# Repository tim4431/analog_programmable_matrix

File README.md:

# Analog Programmable Matrix

A four-input, four-output, DC-coupled analog matrix for programmable addition, subtraction, and signal mixing. A Raspberry Pi Pico sets sixteen static signed coefficients over USB; the signals remain in the analog domain.

$$b_i = \sum_{j=0}^{3} M_{ij}a_j, \qquad -1 \leq M_{ij} \leq 1$$

This first public version contains **PCB D and enclosure M3**, without the added power-indicator LED. It is an **unbuilt prototype**: the 1 MHz bandwidth and approximately 1% gain accuracy are design targets supported by circuit simulations, not measured hardware specifications.

A separate **[LC1 lower-cost 12-bit design](variants/lc1/README.md)** is also included. It preserves the original design and enclosure interface, reduces the listed component count from 428 to 387, and replaces the expensive multiplying DACs. LC1 has its own schematic, PCB, firmware, sourcing notes and simulation evidence. The renders below show the original Revision D.

## PCB and enclosure

These are renders generated from the CAD, not photographs of manufactured hardware.

[Exploded enclosure render](mechanical/analog_matrix_package_m3/renders/enclosure_exploded.png) · [Dimensioned drawing](mechanical/analog_matrix_package_m3/mechanical_dimensions.png)

## Design at a glance

| Item | Design |
| --- | --- |
| Matrix | 4 × 4, independently programmable signed coefficients |
| Signal range | DC through 1 MHz target; ±1 V peak per input |
| Inputs | Four vertical BNCs; high impedance by default |
| Outputs | Four vertical BNCs; up to ±4 V peak **into an external 50 Ω load** |
| Output termination | 49.9 Ω series source resistor; a high-impedance receiver sees approximately twice the loaded voltage |
| Coefficient control | 16-bit multiplying DACs and analog polarity switches |
| Controller | Original Raspberry Pi Pico, MicroPython, USB serial JSON commands |
| Supply | External regulated ±15 V plus USB for the Pico; onboard ±5 V analog regulators |
| PCB | 160 × 170 mm, four copper layers, nominal 1.6 mm FR-4 |
| Enclosure | 180 × 192 × 60 mm; 62.5 mm including feet |
| Cooling | Two 38.1 mm heatsink envelopes; passive ventilation |

## How it works

The input amplifiers generate buffered positive and negative versions of each input. Each matrix cell selects a polarity with a TMUX6219 and sets its magnitude with an AD5544 multiplying DAC and ADA4899-1 transimpedance stage. A summing amplifier combines the four contributions for each output, followed by a THS3091 driver and a 49.9 Ω source resistor. A fifth AD5544 supplies four offset-trim controls.

The Pico changes DAC codes and switch states; it does not digitize or synthesize the waveform. Firmware starts with the outputs muted and temporarily mutes them during coefficient changes. Coefficient and offset calibration are performed through USB commands.

## Open the design

- [KiCad project](pcb/analog_matrix_4x4_rev_d/analog_matrix_4x4.kicad_pro) — open with KiCad 8.0.6 or newer. Keep the included local libraries beside it.
- [Schematic PDF](pcb/analog_matrix_4x4_rev_d/schematic.pdf) — nine sheets: inputs, four output rows, trim, control, power, and index.
- [Firmware and USB protocol](pcb/analog_matrix_4x4_rev_d/firmware/CONTROL.txt).
- [Fabrication and bring-up notes](pcb/analog_matrix_4x4_rev_d/FABRICATION_AND_BRINGUP.txt).
- [Enclosure assembly instructions](mechanical/analog_matrix_package_m3/ASSEMBLY_AND_PRINTING.txt), [STLs](mechanical/analog_matrix_package_m3/print), and [STEP enclosure parts](mechanical/analog_matrix_package_m3/cad).
- [JLCPCB upload files](output/jlcpcb_rev_d) and [procurement status](docs/JLCPCB_ORDER_STATUS.md).

The [Releases page](https://github.com/tim4431/analog_programmable_matrix/releases) contains ZIP downloads, including the complete populated-board and enclosure STEP assemblies. The two large assembly STEP exports are distributed there rather than duplicated in Git.

## Set a matrix

Install the supplied `firmware/main.py` on the original Pico running MicroPython. Apply the analog supplies before USB power, then send newline-terminated JSON commands over the Pico's USB serial console:

```json
{"cmd":"set","matrix":[[1,0,0,0],[0,1,0,0],[0,0,1,0],[0,0,0,1]]}
{"cmd":"arm"}
```

Rows select outputs and columns select inputs. For example, `[0.5,-0.5,0,0]` makes that output half the difference between the first two inputs. Use `{"cmd":"mute"}` to mute the outputs and `{"cmd":"status"}` to read the current state.

The initial gain scale is an estimate. Follow the [calibration procedure](pcb/analog_matrix_4x4_rev_d/firmware/CONTROL.txt) to measure both coefficient signs and each row's offset with the intended 50 Ω loads.

## Validation and limits

The supplied checks report zero KiCad schematic errors, PCB design-rule violations, unrouted connections, or schematic/PCB mismatches. Nominal enclosure collision checks pass, and all three printable parts are watertight, single-shell meshes. The [BNC access review](mechanical/bnc_access_review_no_led/BNC_ACCESS_REVIEW.txt) checks all eight straight-plug positions; the two beside the raised hood need a side grip.

[Circuit-level SPICE results](pcb/analog_matrix_4x4_rev_d/circuit_spice_validation_A2.pdf) show about 0.758% gain reduction at 1 MHz after DC normalization and approximately 119 ns settling to 1% in the nominal row model. Read [MODEL_SCOPE.txt](spice/MODEL_SCOPE.txt): the multiplying-DAC model is approximate, parts of the full-row test are idealized, and the 1 nF load transient remains unresolved. These results do not establish 1% relative accuracy at small coefficients or validate PCB parasitics.

Thermal testing is still required. The analog circuit dissipates roughly 10 W at idle; each ±5 V regulator loses roughly 3 W. The modeled heatsinks are clearance envelopes, not qualified purchased parts. Follow the [thermal calculation and first-article acceptance procedure](mechanical/analog_matrix_package_m3/THERMAL_CALCULATION.txt) before sustained operation.

## Manufacturing

The assembly export contains 406 fitted SMT components, 18 separate through-hole/module items, and four intentionally unpopulated input-termination resistors. Upload these files to JLCPCB:

1. [Gerber_JLCPCB.zip](output/jlcpcb_rev_d/Gerber_JLCPCB.zip)
2. [BOM_JLCPCB.csv](output/jlcpcb_rev_d/BOM_JLCPCB.csv)
3. [CPL_JLCPCB.csv](output/jlcpcb_rev_d/CPL_JLCPCB.csv)

Supplier matching is incomplete. Do not treat the six existing LCSC identifiers as reserved assembly inventory. Check every selected part's package and pin-1 orientation, and obtain CAM acceptance for epoxy-filled/copper-capped via-in-pad fabrication, including the 0.20 mm thermal holes. The [handoff notes](output/jlcpcb_rev_d/START_HERE.txt) describe the exact stack, drill and placement conventions.

The requested initial build is **two assembled boards**. No order has been submitted or paid.

## Reproduce checks and CAD

Run `python tools/verify_release.py` to verify the stored design hash, check reports, BOM/CPL references, and simulation netlist evidence. It checks the delivered files; it does not rerun SPICE or physical tests.

For fresh electrical checks, use KiCad's `kicad-cli sch erc` and `kicad-cli pcb drc --schematic-parity` on the project. The scripts in the project's `tools/` directory compare symbol pins, footprints, and the exported netlist.

Mechanical sources are `mechanical/analog_matrix_package_m3/build_package.py` (CadQuery 2.8) and `render_package.py` (Blender 4.3). The included geometry, models, and PCB texture allow the current assembly and renders to be regenerated. The auxiliary export scripts use KiCad's Python environment and Windows installation paths, which may need adjustment on another system.

Final simulation benches and their recorded results are retained under `spice/`. Manufacturer macromodel downloads are excluded from Git; use `python spice/fetch_models.py` with TI's model downloads and a local LTspice installation, then `python spice/replay.py --bench a2_row_sine_rc.cir`. See [simulation setup](spice/README.md).

## Third-party material

KiCad footprint/model licensing and attribution are included beside the libraries. TI and Analog Devices simulation models retain their manufacturers' terms and are not covered by any implied project-wide license. See [third-party notices](docs/THIRD_PARTY_NOTICES.md). A project-wide license for the original design has not yet been selected.

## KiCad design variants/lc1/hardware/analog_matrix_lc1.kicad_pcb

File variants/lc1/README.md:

# LC1: lower-cost 12-bit analog matrix

LC1 is a separate four-input, four-output programmable analog matrix. It keeps the DC–1 MHz, ±1 V input and ±4 V output into 50 Ω targets of [Revision D](../../pcb/analog_matrix_4x4_rev_d), using less expensive multiplying DACs and more dual/quad packages. Revision D remains available unchanged.

**This is an unbuilt prototype, not a measured 1% instrument.** The nominal circuit simulations meet the amplitude-flatness target, but the cheaper DAC's bandwidth is a typical specification. Actual boards need qualification. Use the LC1 PCB, BOM and firmware together; the parts are not drop-in replacements on Revision D.

## Design changes

Quantities below are per board.

| Function | Original Revision D | LC1 |
| --- | --- | --- |
| Matrix multiplying DACs | 4 × AD5544, 16 bit | 16 × DAC7811, 12 bit |
| Offset DAC | 1 × AD5544 | 1 × MCP4728 |
| Input and summing amplifiers | 16 × OPA810 | 8 × OPA2810 dual |
| Polarity and mute switches | 20 × TMUX6219 | 10 × TMUX6136 dual |
| Offset amplifiers | 4 × OPA197 | 1 × OPA4197 quad |
| Current-to-voltage amplifiers | 16 × ADA4899-1 | Same |
| 50 Ω output drivers | 4 × THS3091 | Same |
| IC packages, including controller/regulators | 71 | 62 |
| Total listed components, including 4 DNP resistors | 428 | 387 |

That is **41 fewer components and 9 fewer IC packages** overall, even though the economical matrix DACs are single-channel devices. The fast current-to-voltage stages and high-current output drivers are retained to avoid a much riskier signal-path simplification. Connector clearances, 160 × 170 mm outline, power inlet, mounting holes and the existing [M3 enclosure](../../mechanical/analog_matrix_package_m3) are retained. The board is not thermally requalified by this revision; use the original insulated heatsinks and ventilation.

## Files

- [KiCad project](hardware/analog_matrix_lc1.kicad_pro), [schematic PDF](hardware/schematic.pdf), [PCB](hardware/analog_matrix_lc1.kicad_pcb).
- [Simulation review PDF](simulation/report/LC1_simulation_review.pdf), [recorded results](simulation/results.json), [model limitations](simulation/MODEL_SCOPE.txt).
- [LC1 Pico firmware](firmware/main.py) and [control/calibration instructions](firmware/CONTROL.md).
- [Gerber ZIP](assembly/Gerber_JLCPCB_LC1.zip), [SMT BOM](assembly/BOM_JLCPCB.csv), [placement file](assembly/CPL_JLCPCB.csv), and [assembly instructions](assembly/START_HERE.txt).
- [Purchasing comparison and sourcing limitations](SOURCING.md).

## PCB and shared enclosure

These CAD renders show LC1's component population in the existing M3 enclosure; they are not photographs or proof of electrical performance.

[Exploded view](mechanical/renders/enclosure_exploded.png) · [Mechanical clearance checks](mechanical/mechanical_checks.json)

## Electrical operation

Each input is buffered and split into matched positive and negative paths. A TMUX6136 channel selects polarity, a DAC7811 sets magnitude, and an ADA4899 converts the DAC current to a voltage. Four weighted voltages enter each row summer. A muted/unmuted output stage drives a 49.9 Ω series resistor and the external 50 Ω load.

Inputs are high impedance. The quoted output amplitudes require **an external 50 Ω termination**; a high-impedance receiver sees approximately twice that voltage. Analog ±15 V power and USB are both required. Apply analog power before USB; USB ground is common with signal ground.

The multiplying DACs are genuinely multiplying converters, so negative and positive DC inputs remain valid. An inexpensive ordinary voltage-output DAC is used only for DC offset correction. Twelve-bit coefficient magnitude steps are approximately 0.026% after gain headroom. Calibrate positive and negative gain separately for every matrix entry. Small-coefficient relative error and deep cancellation are not specified.

The TMUX6136 uses ±15 V supplies, with 120 Ω typical on resistance included in the model. Calibration absorbs its static attenuation. Compensation is 1.0 pF C0G ±0.1 pF at each ADA4899; the model includes additional stray capacitance. Row summing feedback is 549 Ω, providing coefficient calibration headroom.

The MCP4728 uses its internal 2.048 V reference and gain of one. OPA4197 stages invert and filter its outputs with 10 kΩ/10 nF feedback. Trim code 2500 gives approximately −1.25 V at a trim amplifier. Nominal loaded output trim is about 55 µV/code; the output correction range is approximately −138 to +88 mV, before individual device offsets.

## Validation and limits

The schematic passes KiCad ERC and an independent pin-to-net comparison with zero errors. The routed PCB passes native DRC with **zero violations, zero incomplete connections and zero schematic mismatches**. Gerbers, BOM and placements are checked against the released PCB hash. [Recorded checks](assembly/assembly_checks.json)

The inner ground layer has one continuous filled region and carries no routed signal or power tracks. All 16 DAC current-output connections stay on the top layer, have no vias, and are approximately 5.16 mm long. Power traces were widened where clearance allowed; local pin escapes remain narrower. [Layout review](hardware/layout_review.json)

Host firmware tests cover bit ordering, DAC commands, startup muting, input validation and bus-error muting. The simulation report contains 35 completed, hash-checked cases:

- Nominal 1 MHz magnitude droop: 0.70% positive, 0.72% negative.
- Modeled resistor/capacitance corner: 0.86% droop.
- Minimum modeled feedback phase margin: 57.5°.
- Full four-input step settles within 1% in about 118 ns (50 Ω + 20 pF) or 181 ns (50 Ω + 1 nF).
- A deliberately reduced 5 MHz DAC-bandwidth assumption produces 2.15% droop and **fails** the 1% target.

These are circuit-model results. DAC bandwidth and switches use simplified models, and PCB parasitics, crosstalk, noise, temperature drift and power sequencing are not fully modeled. Do not treat the 35 completed cases as a claim that all hypothetical corners meet specification.

## Reproduction

The released KiCad files are the editable design. `tools/build_design.py` derives LC1 schematic sheets from the unchanged original; `tools/build_board.py` produces a placement/routing seed, **not a finished routed board**. Do not run the seed generator over a routed PCB you wish to keep.

Circuit models are intentionally excluded from Git where vendor licenses apply. Fetch the original amplifier models with `../../spice/fetch_models.py`, then use `tools/fetch_models.py` for LC1-specific models. Run `tools/simulate.py` with LTspice installed. `tools/test_firmware.py` tests the LC1 firmware without a physical Pico. `tools/make_report.py` consumes the recorded raw files and requires NumPy, Matplotlib and ReportLab.

Run `python variants/lc1/tools/verify_release.py` from the repository root to check the stored release evidence, source hashes, manufacturing exports and firmware. This does not rerun SPICE or replace hardware qualification. The existing Revision D JLCPCB order was not changed; LC1 needs its own quote and part matching.

See the original repository license. Imported KiCad libraries retain their separate library license.

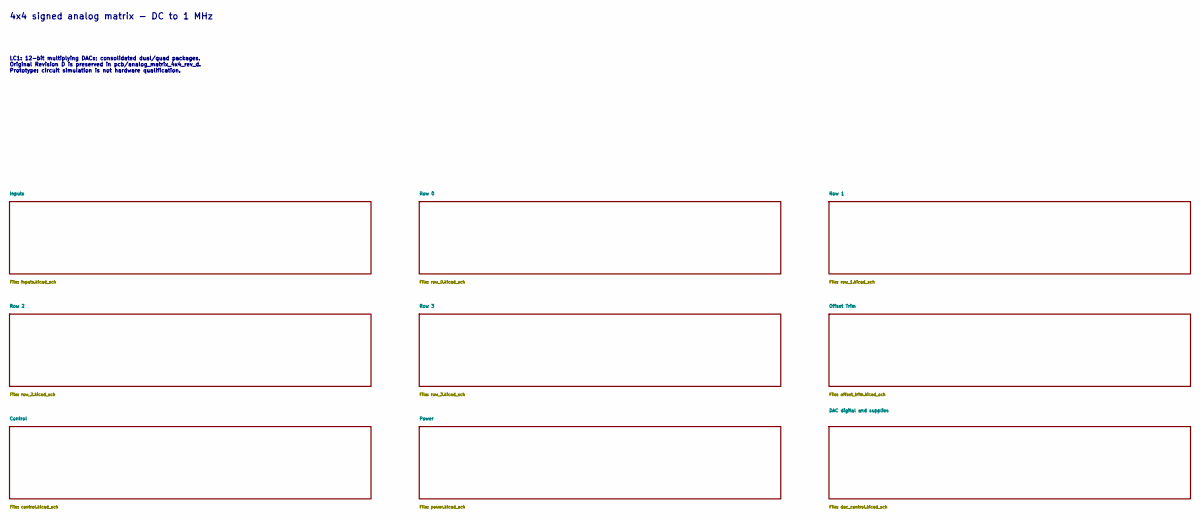
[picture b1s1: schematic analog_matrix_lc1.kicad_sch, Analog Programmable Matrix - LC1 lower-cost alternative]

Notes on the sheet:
4x4 signed analog matrix - DC to 1 MHz
LC1: 12-bit multiplying DACs; consolidated dual/quad packages. Original Revision D is preserved in pcb/analog_matrix_4x4_rev_d. Prototype: circuit simulation is not hardware qualification.

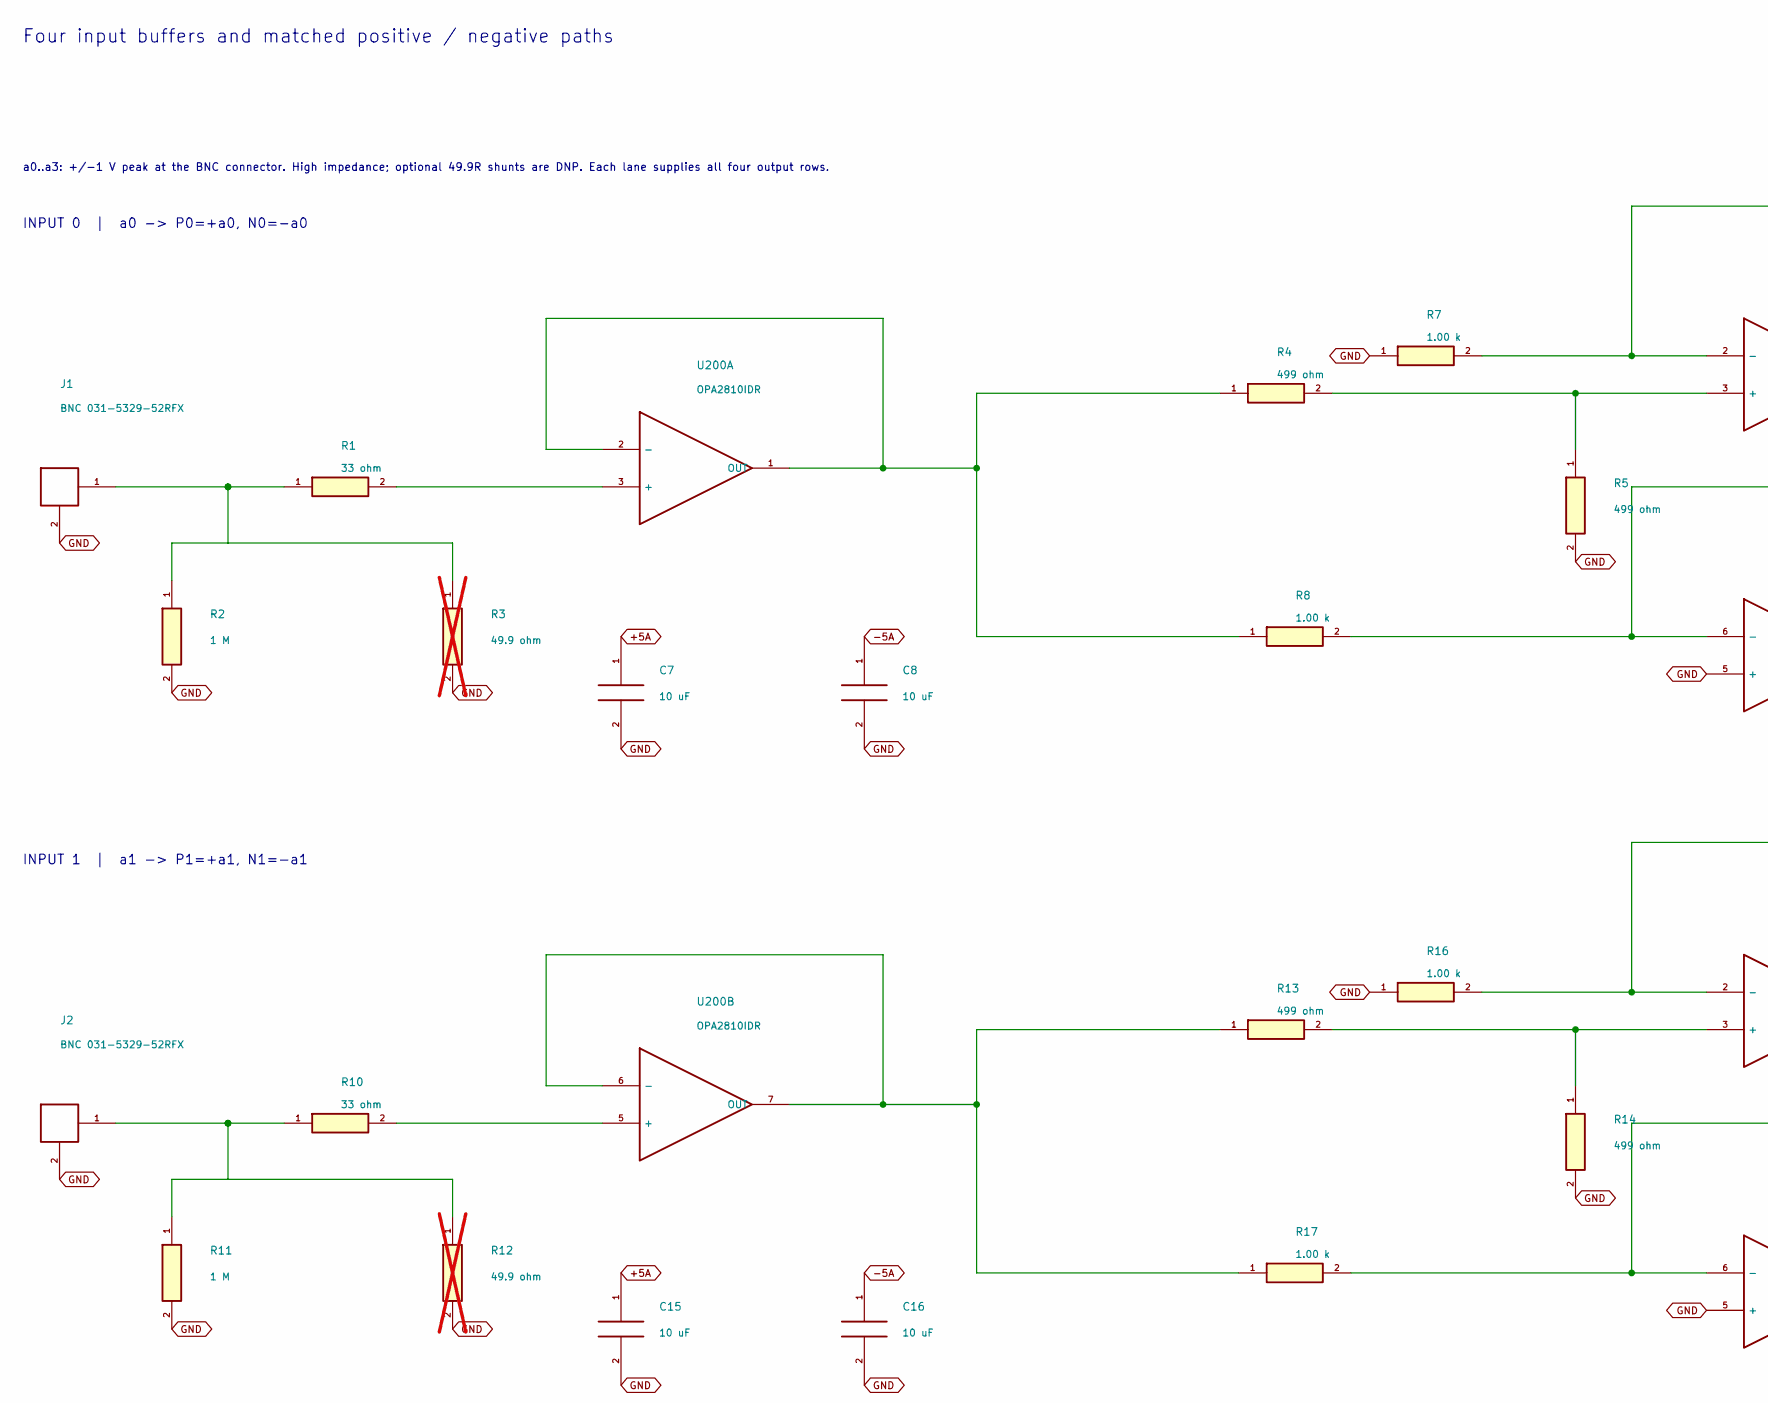
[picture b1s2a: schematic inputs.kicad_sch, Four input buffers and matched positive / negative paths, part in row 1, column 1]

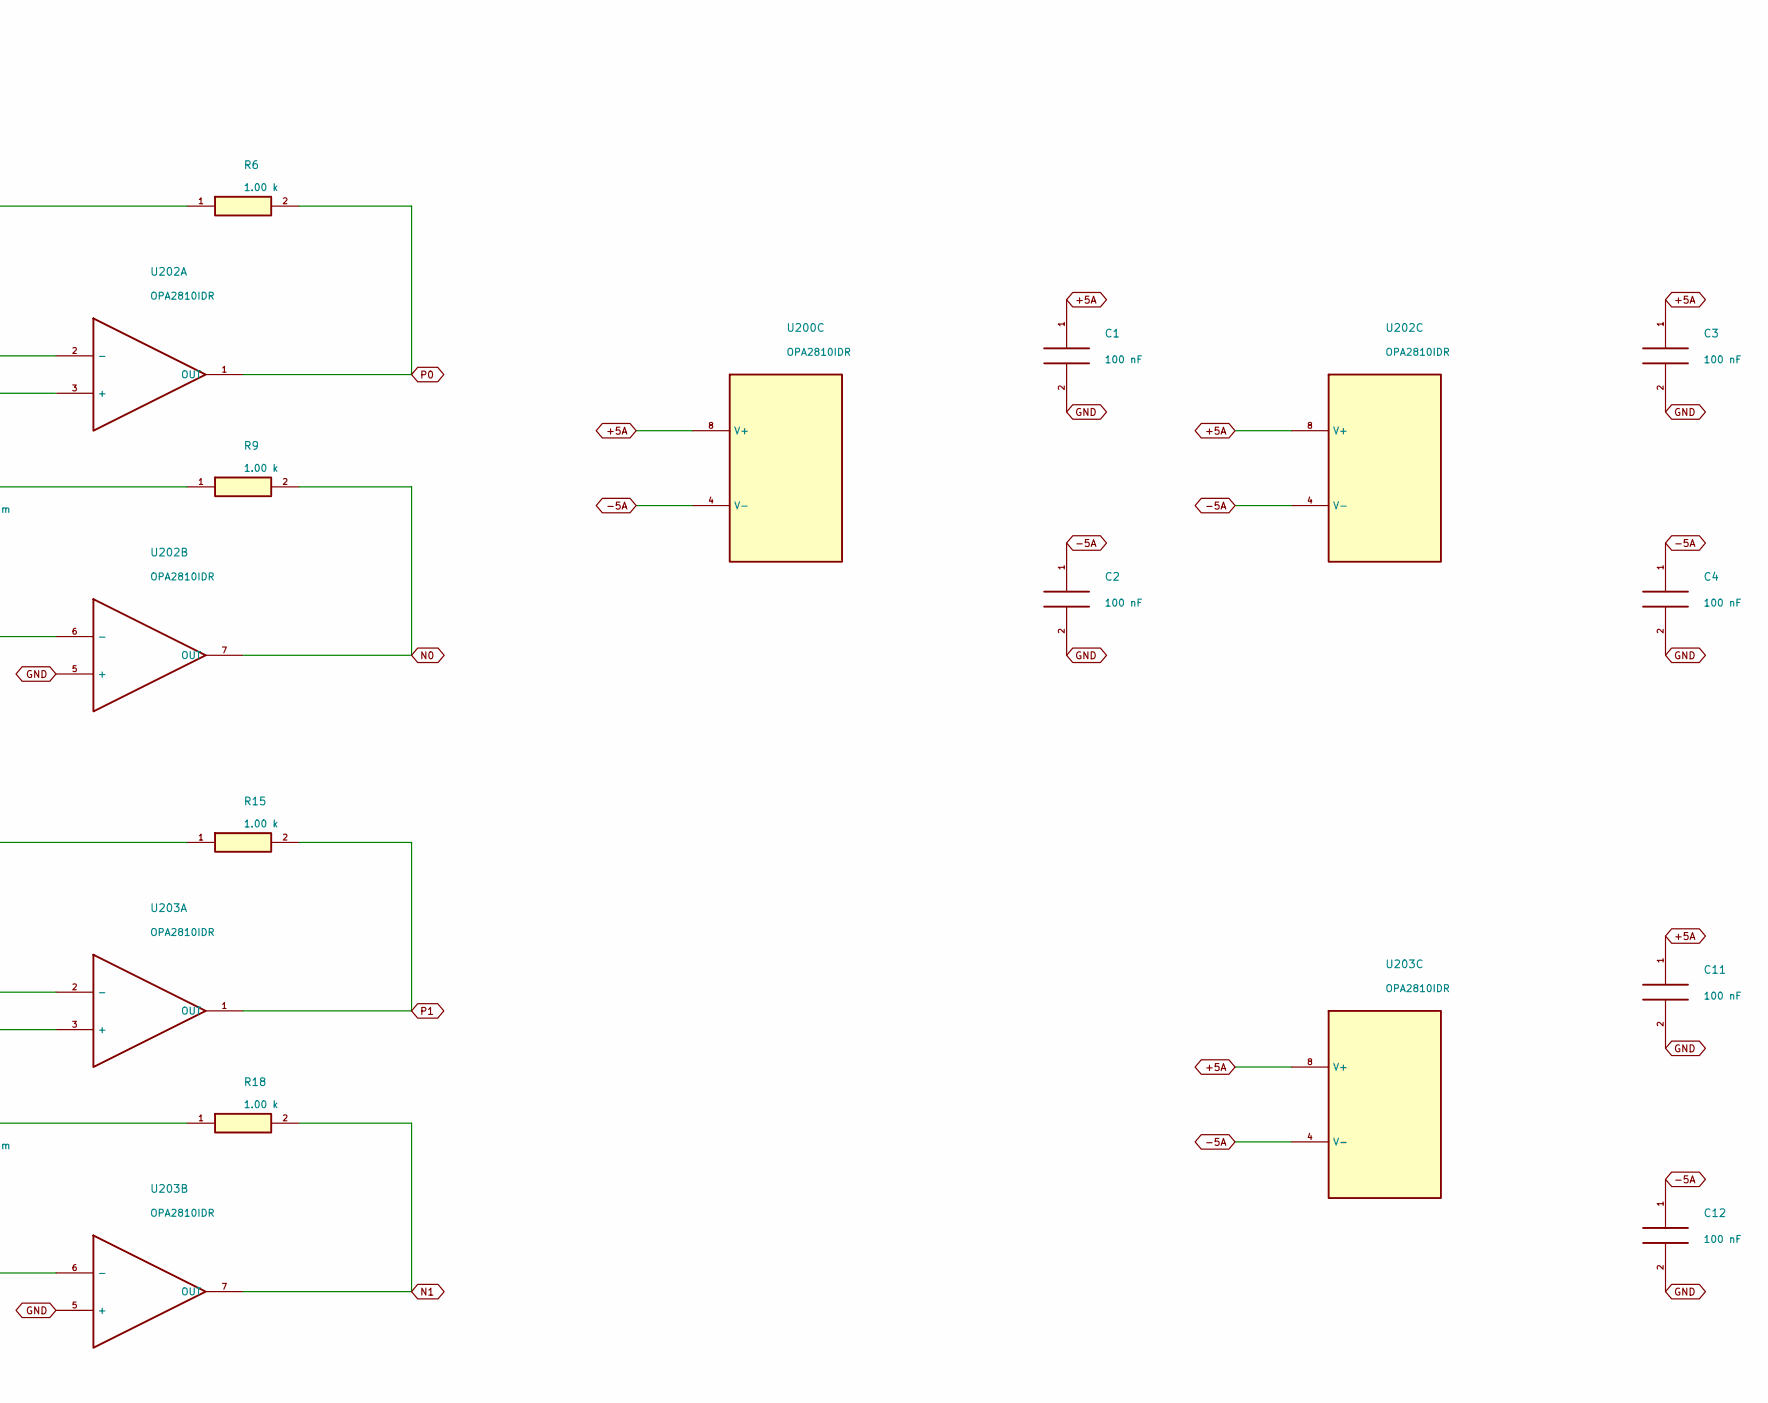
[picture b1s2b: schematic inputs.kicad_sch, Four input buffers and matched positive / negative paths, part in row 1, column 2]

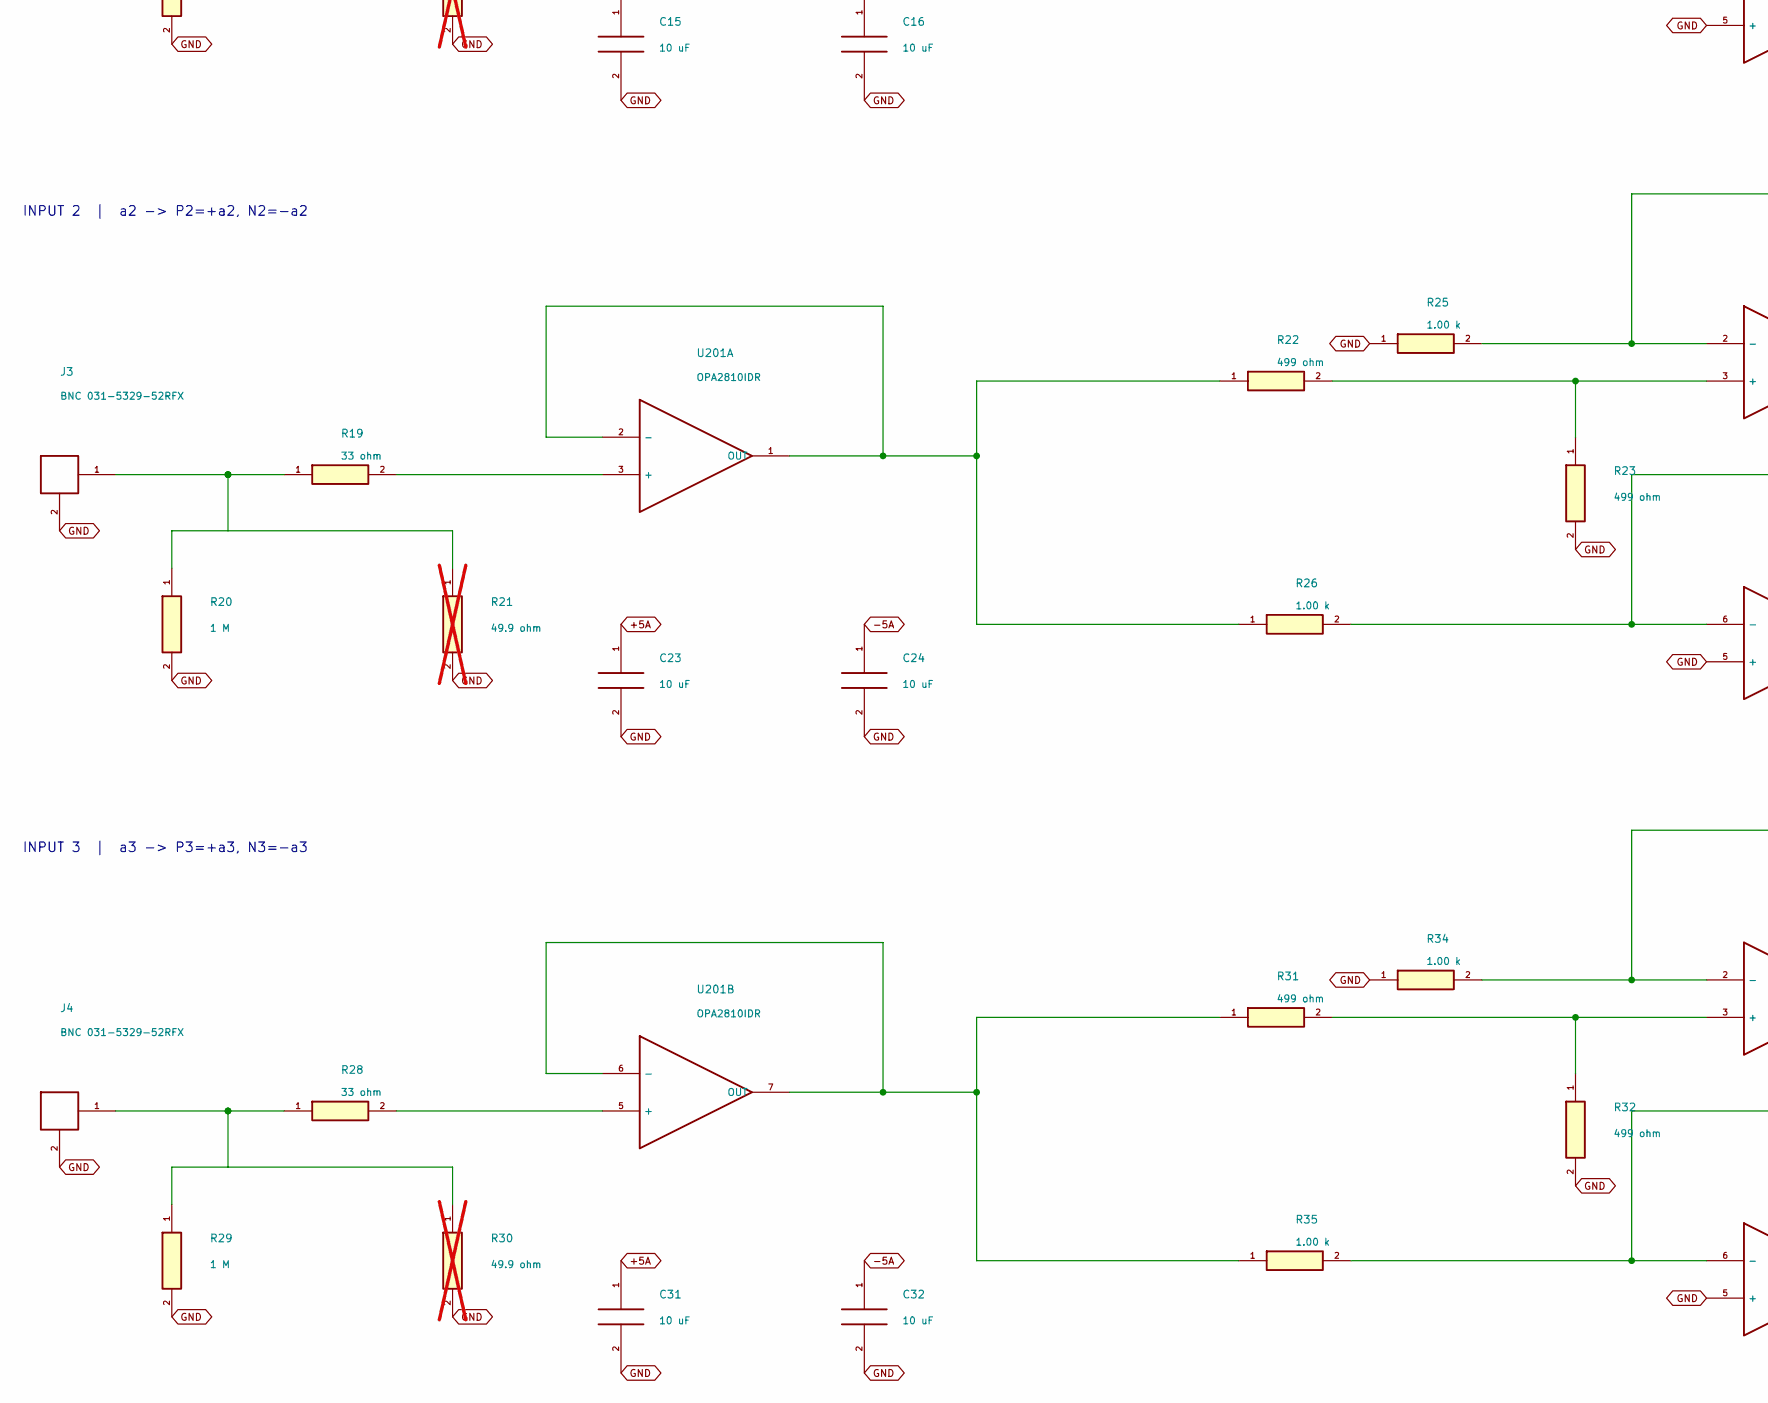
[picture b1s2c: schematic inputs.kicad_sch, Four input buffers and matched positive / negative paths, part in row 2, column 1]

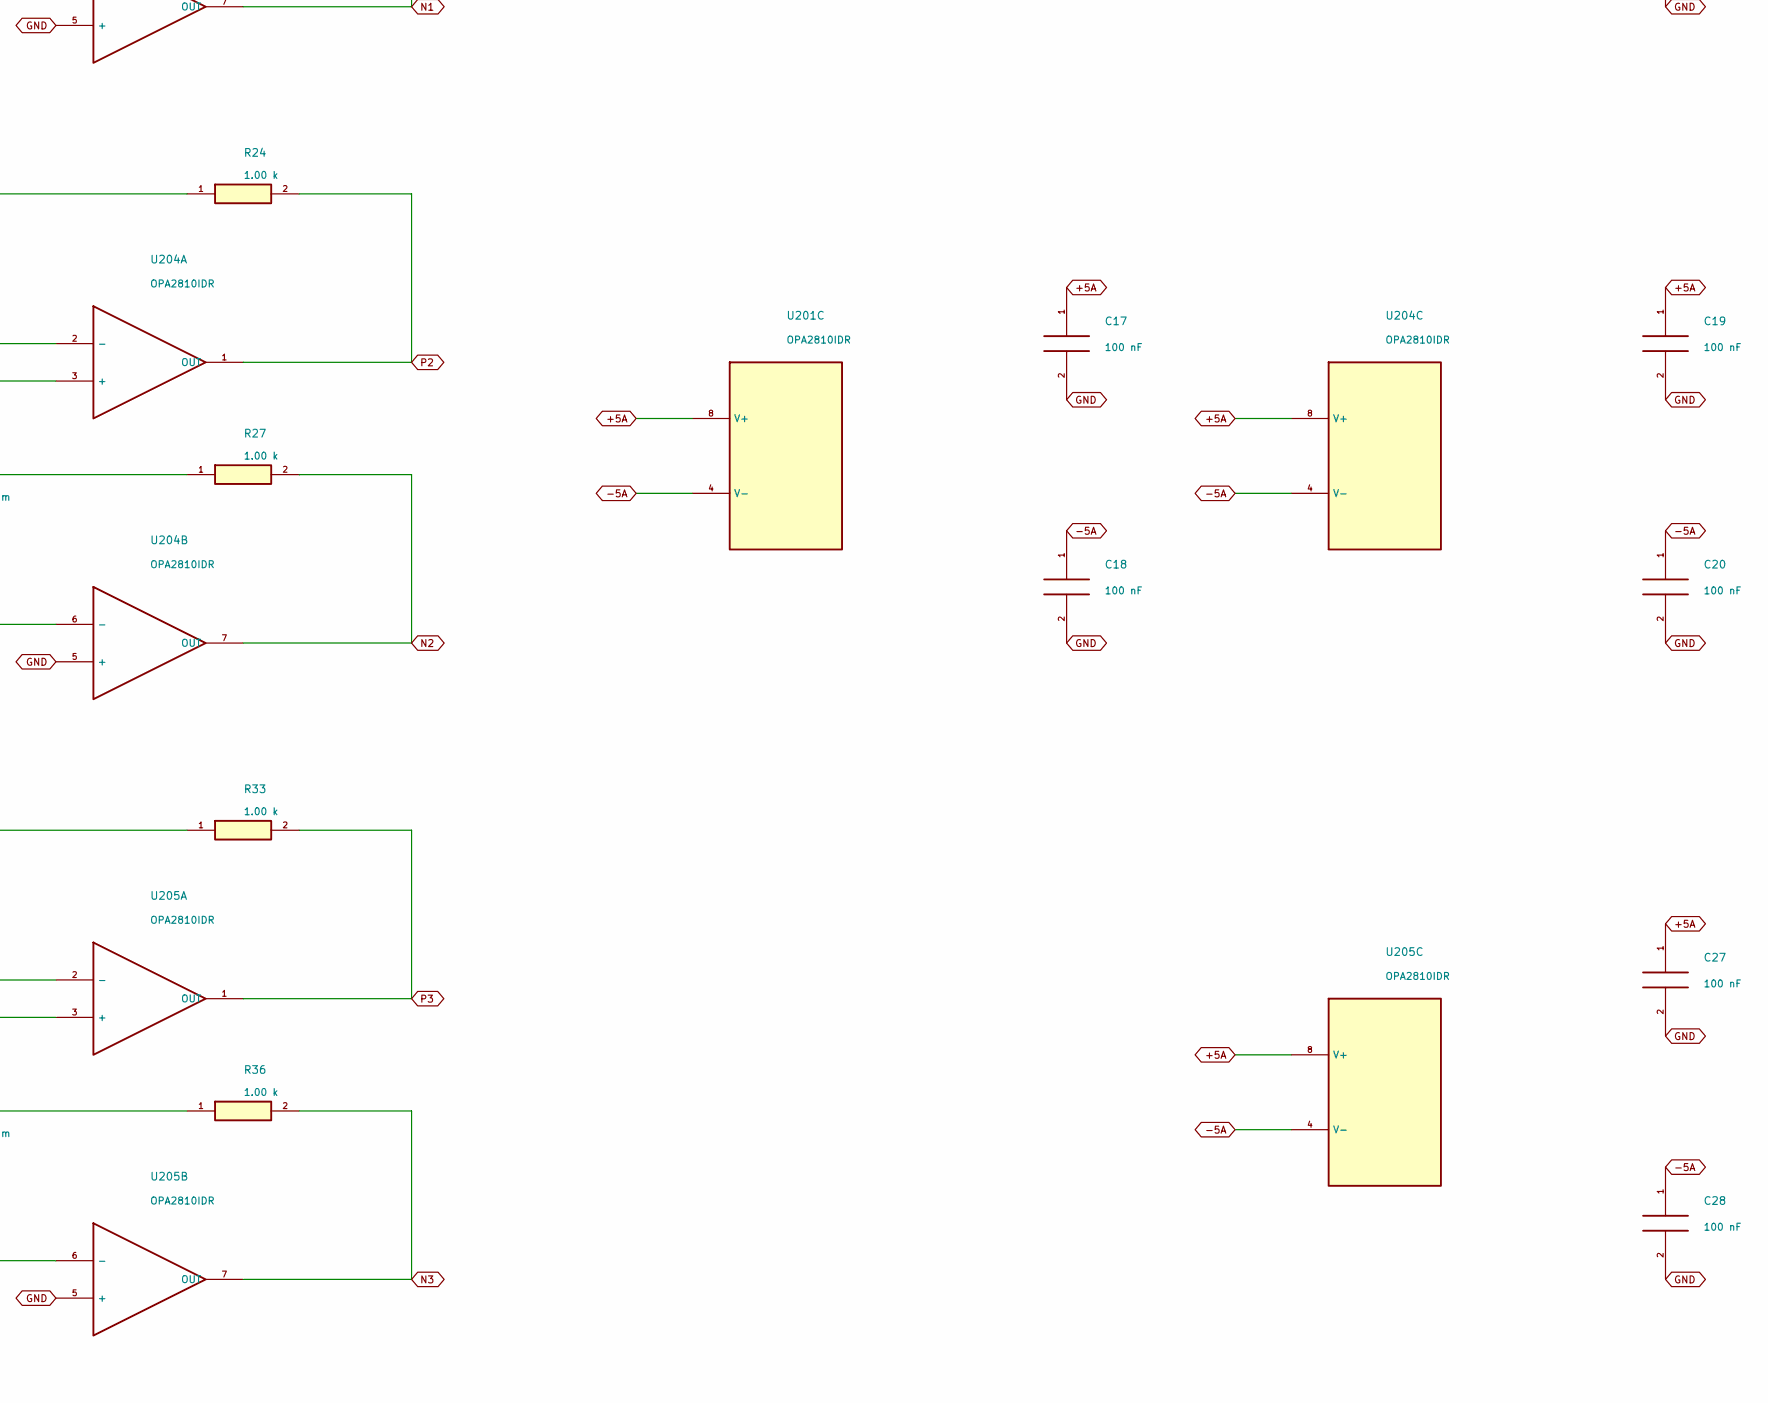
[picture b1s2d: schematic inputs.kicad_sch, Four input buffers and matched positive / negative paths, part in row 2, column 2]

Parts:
C1, C2, C3, C4, C11, C12, C17, C18, C19, C20, C27, C28: 100 nF; C_0603_1608Metric; Rating 25V X7R minimum; effective C after bias
C7, C8, C15, C16, C23, C24, C31, C32: 10 uF; C_0805_2012Metric; Rating 25V X7R minimum; effective C after bias
J1, J2, J3, J4: BNC 031-5329-52RFX; BNC_Amphenol_031-5329-52RFX_Vertical
R1, R10, R19, R28: 33 ohm; R_0603_1608Metric; Rating 0.1%, <=25ppm/C; 0.1W minimum
R2, R11, R20, R29: 1 M; R_0603_1608Metric; Rating 0.1%, <=25ppm/C; 0.1W minimum
R3, R12, R21, R30: 49.9 ohm; R_0603_1608Metric; Rating 0.1%, <=25ppm/C; 0.1W minimum; not fitted
R4, R5, R13, R14, R22, R23, R31, R32: 499 ohm; R_0603_1608Metric; Rating 0.1%, <=25ppm/C; 0.1W minimum
R6, R7, R8, R9, R15, R16, R17, R18, R24, R25, R26, R27, R33, R34, R35, R36: 1.00 k; R_0603_1608Metric; Rating 0.1%, <=25ppm/C; 0.1W minimum
U200, U201, U202, U203, U204, U205: OPA2810IDR; SOIC-8_3.9x4.9mm_P1.27mm

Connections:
+5A: C1.1, C3.1, C7.1, C11.1, C15.1, C17.1, C19.1, C23.1, C27.1, C31.1, U200.8 (V+), U201.8 (V+), U202.8 (V+), U203.8 (V+), U204.8 (V+), U205.8 (V+); also elsewhere on the board
-5A: C2.1, C4.1, C8.1, C12.1, C16.1, C18.1, C20.1, C24.1, C28.1, C32.1, U200.4 (V-), U201.4 (V-), U202.4 (V-), U203.4 (V-), U204.4 (V-), U205.4 (V-); also elsewhere on the board
GND: C1.2, C2.2, C3.2, C4.2, C7.2, C8.2, C11.2, C12.2, C15.2, C16.2, C17.2, C18.2, C19.2, C20.2, C23.2, C24.2, C27.2, C28.2, C31.2, C32.2, J1.2, J2.2, J3.2, J4.2, R2.2, R3.2, R5.2, R7.1, R11.2, R12.2, R14.2, R16.1, R20.2, R21.2, R23.2, R25.1, R29.2, R30.2, R32.2, R34.1, U202.5 (+), U203.5 (+), U204.5 (+), U205.5 (+); also elsewhere on the board
N0: R9.2, U202.7 (OUT); also elsewhere on the board
N1: R18.2, U203.7 (OUT); also elsewhere on the board
N2: R27.2, U204.7 (OUT); also elsewhere on the board
N3: R36.2, U205.7 (OUT); also elsewhere on the board
unnamed: J1.1, R1.1, R2.1, R3.1
unnamed: J2.1, R10.1, R11.1, R12.1
unnamed: J3.1, R19.1, R20.1, R21.1
unnamed: J4.1, R28.1, R29.1, R30.1
unnamed: R1.2, U200.3 (+)
unnamed: R4.1, R8.1, U200.1 (OUT), U200.2 (-)
unnamed: R10.2, U200.5 (+)
unnamed: R13.1, R17.1, U200.6 (-), U200.7 (OUT)
unnamed: R19.2, U201.3 (+)
unnamed: R22.1, R26.1, U201.1 (OUT), U201.2 (-)
unnamed: R28.2, U201.5 (+)
unnamed: R31.1, R35.1, U201.6 (-), U201.7 (OUT)
unnamed: R4.2, R5.1, U202.3 (+)
unnamed: R6.1, R7.2, U202.2 (-)
unnamed: R8.2, R9.1, U202.6 (-)
unnamed: R13.2, R14.1, U203.3 (+)
unnamed: R15.1, R16.2, U203.2 (-)
unnamed: R17.2, R18.1, U203.6 (-)
unnamed: R22.2, R23.1, U204.3 (+)
unnamed: R24.1, R25.2, U204.2 (-)
unnamed: R26.2, R27.1, U204.6 (-)
unnamed: R31.2, R32.1, U205.3 (+)
unnamed: R33.1, R34.2, U205.2 (-)
unnamed: R35.2, R36.1, U205.6 (-)
P0: R6.2, U202.1 (OUT); also elsewhere on the board
P1: R15.2, U203.1 (OUT); also elsewhere on the board
P2: R24.2, U204.1 (OUT); also elsewhere on the board
P3: R33.2, U205.1 (OUT); also elsewhere on the board

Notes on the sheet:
Four input buffers and matched positive / negative paths
a0..a3: +/-1 V peak at the BNC connector. High impedance; optional 49.9R shunts are DNP. Each lane supplies all four output rows.
INPUT 0 | a0 -> P0=+a0, N0=-a0
INPUT 1 | a1 -> P1=+a1, N1=-a1
INPUT 2 | a2 -> P2=+a2, N2=-a2
INPUT 3 | a3 -> P3=+a3, N3=-a3
